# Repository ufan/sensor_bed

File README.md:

# sensor_bed

## Compaticble MCU module
All pro-micro compatible module, recommended: [nrfmacro-lite](https://github.com/ufan/nrfmicro/tree/one-more-row)

## Available sensors
- trackball sensor: pmw3610
- blackberry trackball module
- joystick: cts-254
- encoder: kailh red
- capacitive slider: cap1203 or xw06a
- display: sharp memory lcd 1.1 inch

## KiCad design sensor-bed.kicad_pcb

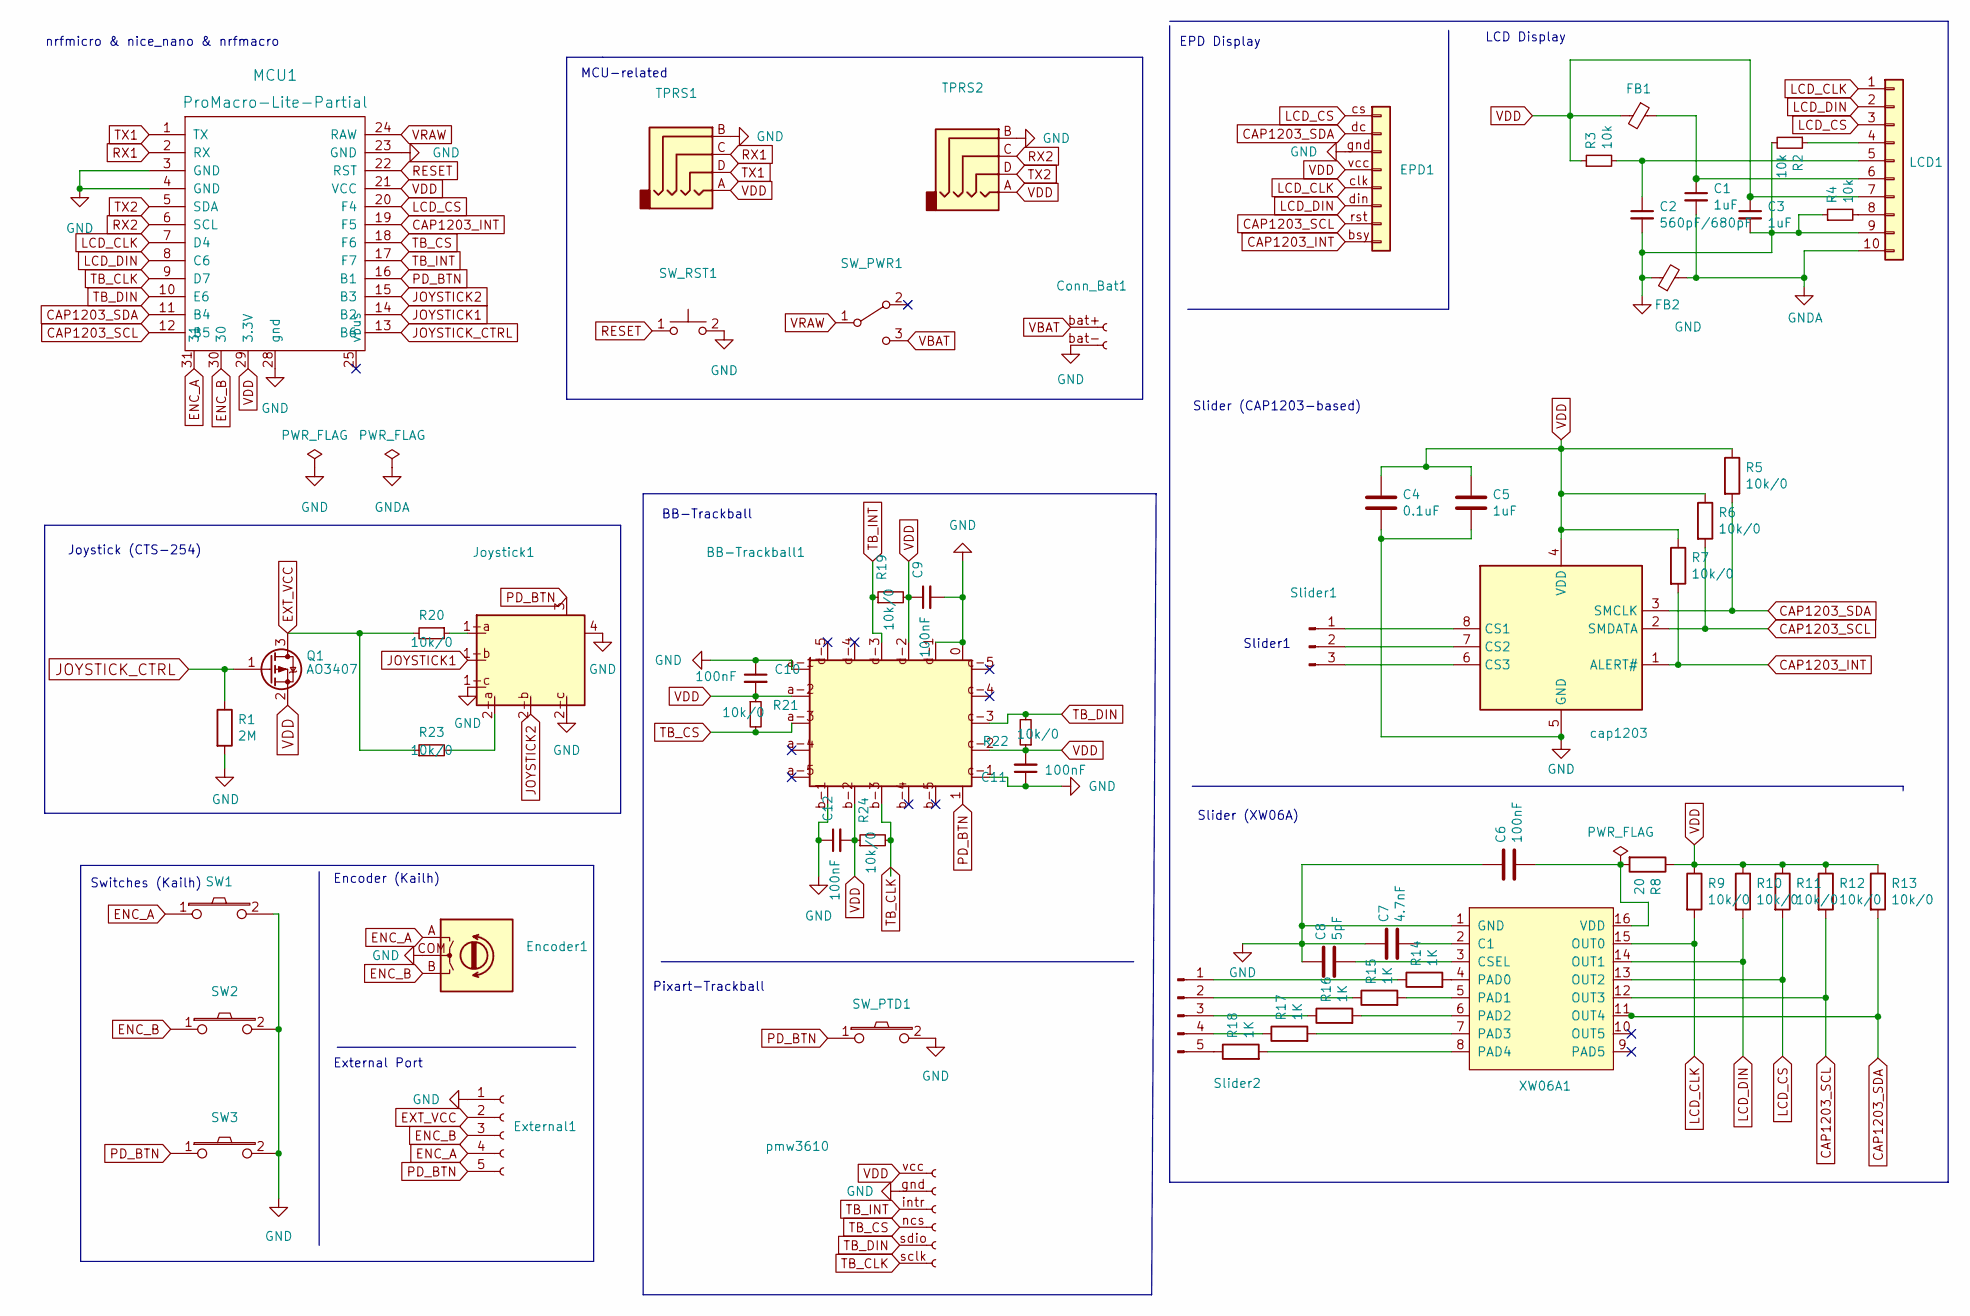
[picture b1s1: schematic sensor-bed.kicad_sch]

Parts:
BB-Trackball1: BB-Trackball; BB-Trackball-EVQWJN
C1, C3: 1uF; C_0603_1608Metric_Pad1.08x0.95mm_HandSolder; LCSC C15849
C2: 560pF/680pF; C_0603_1608Metric_Pad1.08x0.95mm_HandSolder; LCSC C84721
C4: 0.1uF; C_0603_1608Metric
C5: 1uF; C_0603_1608Metric
C6, C9, C10, C11, C12: 100nF; C_0603_1608Metric
C7: 4.7nF; C_0603_1608Metric
C8: 5pF; C_0603_1608Metric
Conn_Bat1: Conn_01x02_Female
EPD1: Conn_01x08
Encoder1: RotaryEncoder; Encoder-Kailh
External1: Conn_01x05_Female
FB1, FB2: Ferrite_Bead_Small; R_0805_2012Metric_Pad1.20x1.40mm_HandSolder; LCSC C1017
Joystick1: CTS-254-Joystick
LCD1: Conn_01x10; Hirose_FH12-10S-0.5SH_1x10-1MP_P0.50mm_Horizontal; LCSC C506791
MCU1: ProMacro-Lite-Partial; ProMacroLite_Partial
Q1: AO3407; SOT-23
R1: 2M; R_0603_1608Metric
R2, R3, R4: 10k; R_0603_1608Metric_Pad0.98x0.95mm_HandSolder; LCSC C25804
R5, R6, R7, R9, R10, R11, R12, R13, R19, R20, R21, R22, R23, R24: 10k/0; R_0603_1608Metric
R8: 20; R_0603_1608Metric
R14, R15, R16, R17, R18: 1K; R_0603_1608Metric
SW1, SW2, SW3: SW_PUSH-kbd; Kailh_Choc_Hotplug
SW_PTD1: D2LS-21; D2LS-21-Omron
SW_PWR1: SW_Battery-kbd; NSI-10HS-slider-switch
SW_RST1: SW_RESET-kbd; YD-3414-Button
Slider1: Conn_01x03_Male; TouchSlider-3_36x12mm
Slider2: Conn_01x05_Male; TouchSlider-5_40x12mm
TPRS1, TPRS2: SK_TPRS-kbd; TRRS-PJ-320A
XW06A1: XW06A-SOP16L; XW06A
cap1203: CAP1203; SOIC-8_3.9x4.9mm_P1.27mm
pmw3610: Conn_01x06_Female; PMW3610-Ref-EdgeCut

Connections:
CAP1203_INT: EPD1.bsy, MCU1.19 (F5), R7.2, cap1203.1 (ALERT#)
CAP1203_SCL: EPD1.rst, MCU1.12 (B5), R6.2, R12.2, XW06A1.12 (OUT3), cap1203.2 (SMDATA)
CAP1203_SDA: EPD1.dc, MCU1.11 (B4), R5.2, R13.2, XW06A1.11 (OUT4), cap1203.3 (SMCLK)
ENC_A: Encoder1.A, External1.4, MCU1.31, SW1.1
ENC_B: Encoder1.B, External1.3, MCU1.30, SW2.1
EXT_VCC: External1.2, Q1.3 (D), R20.2, R23.1
GND: BB-Trackball1.0, BB-Trackball1.a-1 (A-GND), BB-Trackball1.b-1 (B-GND), BB-Trackball1.c-1 (C-GND), BB-Trackball1.d-1 (D-GND), C2.2, C3.2, C4.2, C5.2, C6.1, C7.1, C8.1, C9.2, C10.1, C11.1, C12.1, Conn_Bat1.bat-, EPD1.gnd, Encoder1.COM, External1.1, FB2.1, Joystick1.1-c (1-C), Joystick1.2-c (2-C), Joystick1.4, LCD1.9, MCU1.3 (GND), MCU1.4 (GND), MCU1.23 (GND), MCU1.28 (gnd), R1.2, R2.2, R4.1, SW1.2, SW2.2, SW3.2, SW_PTD1.2, SW_RST1.2, TPRS1.B, TPRS2.B, XW06A1.1 (GND), cap1203.5 (GND), pmw3610.gnd
GNDA: C1.2, FB2.2, LCD1.10
JOYSTICK1: Joystick1.1-b (1-B), MCU1.14 (B2)
JOYSTICK2: Joystick1.2-b (2-B), MCU1.15 (B3)
JOYSTICK_CTRL: MCU1.13 (B6), Q1.1 (G), R1.1
LCD_CLK: EPD1.clk, LCD1.1, MCU1.7 (D4), R9.2, XW06A1.15 (OUT0)
LCD_CS: EPD1.cs, LCD1.3, MCU1.20 (F4), R11.2, XW06A1.13 (OUT2)
LCD_DIN: EPD1.din, LCD1.2, MCU1.8 (C6), R10.2, XW06A1.14 (OUT1)
unnamed: C1.1, FB1.1, LCD1.6
unnamed: C2.1, LCD1.5, R3.2
unnamed: C6.2, R8.2, XW06A1.16 (VDD)
unnamed: C7.2, XW06A1.2 (C1)
unnamed: C8.2, XW06A1.3 (CSEL)
unnamed: Joystick1.1-a (1-A), R20.1
unnamed: Joystick1.2-a (2-A), R23.2
unnamed: LCD1.4, R2.1
unnamed: LCD1.8, R4.2
unnamed: R14.1, Slider2.1
unnamed: R14.2, XW06A1.4 (PAD0)
unnamed: R15.1, Slider2.2
unnamed: R15.2, XW06A1.5 (PAD1)
unnamed: R16.1, Slider2.3
unnamed: R16.2, XW06A1.6 (PAD2)
unnamed: R17.1, Slider2.4
unnamed: R17.2, XW06A1.7 (PAD3)
unnamed: R18.1, Slider2.5
unnamed: R18.2, XW06A1.8 (PAD4)
unnamed: Slider1.1, cap1203.8 (CS1)
unnamed: Slider1.2, cap1203.7 (CS2)
unnamed: Slider1.3, cap1203.6 (CS3)
PD_BTN: BB-Trackball1.1, External1.5, Joystick1.3, MCU1.16 (B1), SW3.1, SW_PTD1.1
RESET: MCU1.22 (RST), SW_RST1.1
RX1: MCU1.2 (RX), TPRS1.C
RX2: MCU1.6 (SCL), TPRS2.C
TB_CLK: BB-Trackball1.b-3 (B-VOUT), MCU1.9 (D7), R24.2, pmw3610.sclk
TB_CS: BB-Trackball1.a-3 (A-VOUT), MCU1.18 (F6), R21.2, pmw3610.ncs
TB_DIN: BB-Trackball1.c-3 (C-VOUT), MCU1.10 (E6), R22.2, pmw3610.sdio
TB_INT: BB-Trackball1.d-3 (D-VOUT), MCU1.17 (F7), R19.1, pmw3610.intr
TX1: MCU1.1 (TX), TPRS1.D
TX2: MCU1.5 (SDA), TPRS2.D
VBAT: Conn_Bat1.bat+, SW_PWR1.3 (C)
VDD: BB-Trackball1.a-2 (A-VIN), BB-Trackball1.b-2 (B-VIN), BB-Trackball1.c-2 (C-VIN), BB-Trackball1.d-2 (D-VIN), C3.1, C4.1, C5.1, C9.1, C10.2, C11.2, C12.2, EPD1.vcc, FB1.2, LCD1.7, MCU1.21 (VCC), MCU1.29 (3.3V), Q1.2 (S), R3.1, R5.1, R6.1, R7.1, R8.1, R9.1, R10.1, R11.1, R12.1, R13.1, R19.2, R21.1, R22.1, R24.1, TPRS1.A, TPRS2.A, cap1203.4 (VDD), pmw3610.vcc
VRAW: MCU1.24 (RAW), SW_PWR1.1

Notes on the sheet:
Slider (CAP1203-based)
EPD Display
MCU-related
Switches (Kailh)
Joystick (CTS-254)
nrfmicro & nice_nano & nrfmacro
External Port
Encoder (Kailh)
Slider (XW06A)
LCD Display
BB-Trackball
Slider1
Pixart-Trackball

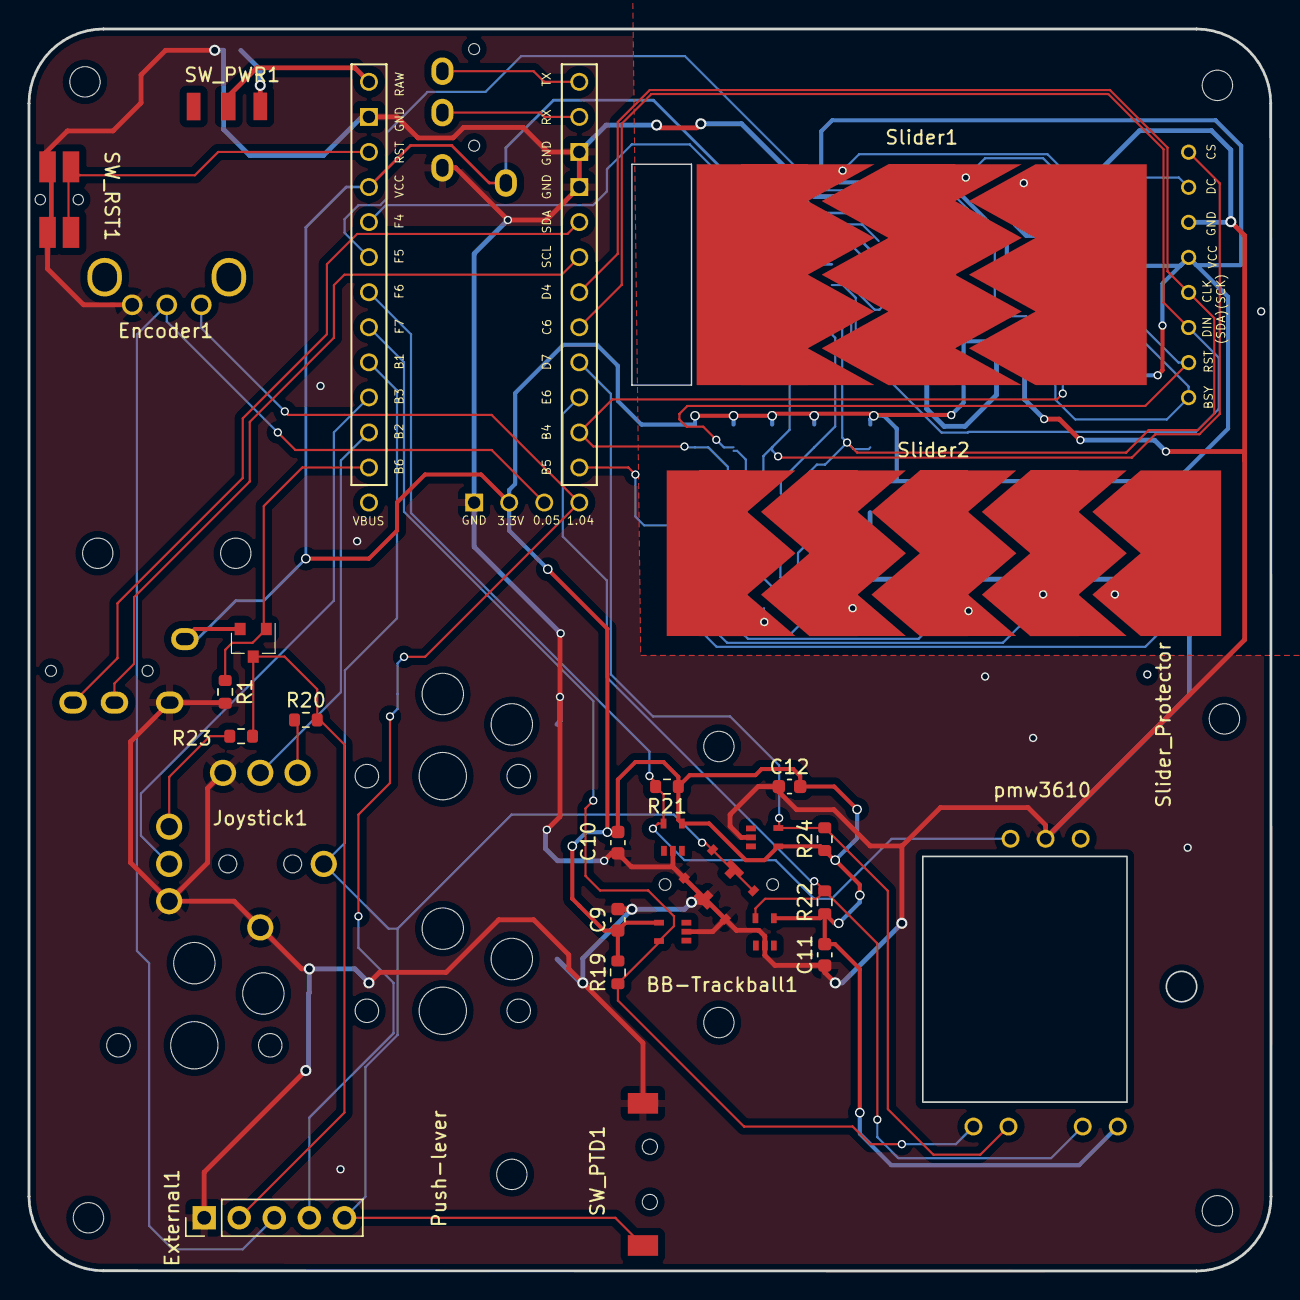
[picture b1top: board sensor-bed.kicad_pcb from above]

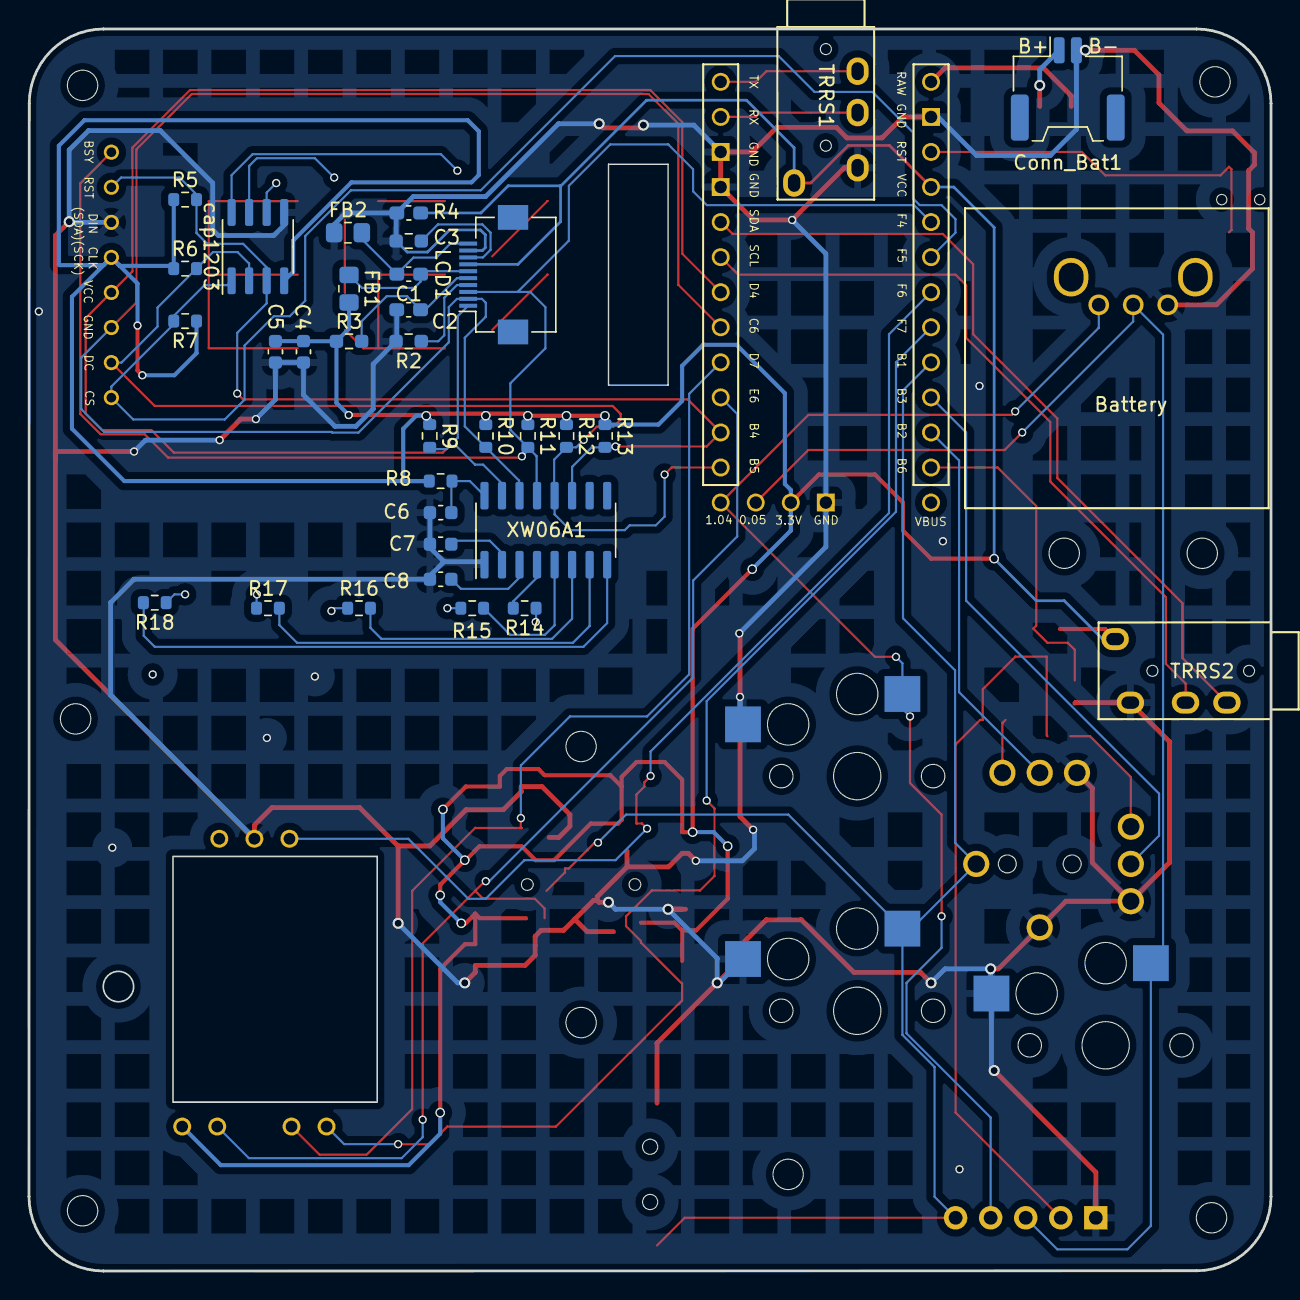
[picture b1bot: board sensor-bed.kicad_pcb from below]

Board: 2 copper layers, 90.0 x 90.0 mm, 70 parts (33 on the bottom side), 49 nets.

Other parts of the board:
BB_Case1, BB_Case2: MountingHole_2.2mm_M2
MtHole1, MtHole2, MtHole3, MtHole4: MountingHole_2.2mm_M2
Push-lever: MountingHole_2.2mm_M2
Roller_Stand1, Roller_Stand2: MountingHole_2.2mm_M2
Slider_Protector: MountingHole_2.2mm_M2

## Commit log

2022-10-27 add some description
